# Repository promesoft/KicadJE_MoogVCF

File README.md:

# KicadJE_MoogVCF
Based on https://www.yusynth.net/Modular/Commun/MOOGVCF/Moogfilter-sch.jpg

Based on https://www.yusynth.net/Modular/Commun/WAVEFOLDER/new/JHWavefolder-sch.gif

Based on https://www.yusynth.net/Modular/Commun/ADSR/ADSR555-FINAL.gif

# Status - PCB  in the mail
## Initial 
| Stage  | Detail | Status |
| ------------- | ------------- | ------------- |
| create material  | sch/pcb | OK  |
| | gerber | OK |
| production  |   | Ok |
|  | produced | OK |
|  | delivered | Ok |
## Preliminary validation
| Test  | Detail | Status |
| ------------- | ------------- | ------------- |
| Initial Inspection | | OK - silk messed a bit |
| Initial Technical Test | VCF | CV2 signal issue round Jack |
| Initial Technical Test | ADSR | OK |
| Initial Technical Test | WaveFolder | OK |
| Initial Product Test | VCF | Not working due to missing Caps |
| Initial Product Test | ADSR | OK |
| Initial Product Test | Wavefolder | Works nicely |

## Secondary validation
| Test  | Detail | Status |
| ------------- | ------------- |------------- |
| Product Test | CF | VCF - working ok after botch'ed caps added - no self osc|
| Product Test | ADSR | Works fine after added 100k resistors instead of 0R across 100KB pots |
| Product Test | Wavefolder | nice - no adjustments |
| Quality | VCF | Needs tweaking |
| Quality | ADSR | ADSR interacts when turned all the way down|
| Quality | Wavefolder| Nice |
| Long Term Product Test |  |  |
| Power Draw | VCF | 24mA |
| Power Draw | ADSR | mA |
| Power Draw | Wavefolder | 7mA |

## Errata
### Errata - VCF
 * Missing signal path for CV2 on PCB
 * Missing 2 caps from C207 to R226/227

## Issues and Notes
### VCF
* C214 should be 1206 (its a bit difficult to find 22u 0805 in 16v)
* C211 and C212 should be 1206 or bigger (10u 16v potentially sounds better than 0805)

# Pictures

# Inspiration

# Schematic
## Ladder Filter

## Simple 555 ADSR

## WaveFolder

# Inspiration
 http://jhaible.com/legacy/jh_shaper_B.pdf
 
 https://www.yusynth.net/Modular/Commun/WAVEFOLDER/new/JHWavefolder-sch.gif

 https://www.yusynth.net/Modular/Commun/MOOGVCF/Moogfilter-sch.jpg

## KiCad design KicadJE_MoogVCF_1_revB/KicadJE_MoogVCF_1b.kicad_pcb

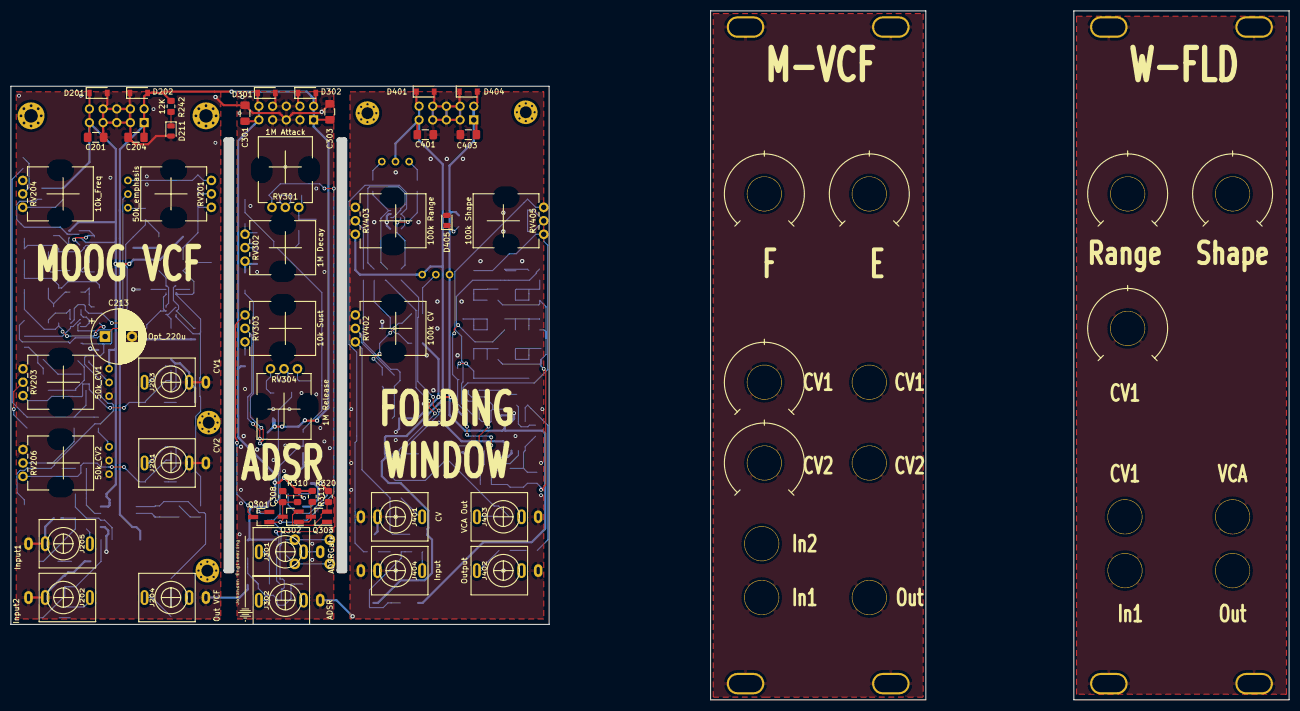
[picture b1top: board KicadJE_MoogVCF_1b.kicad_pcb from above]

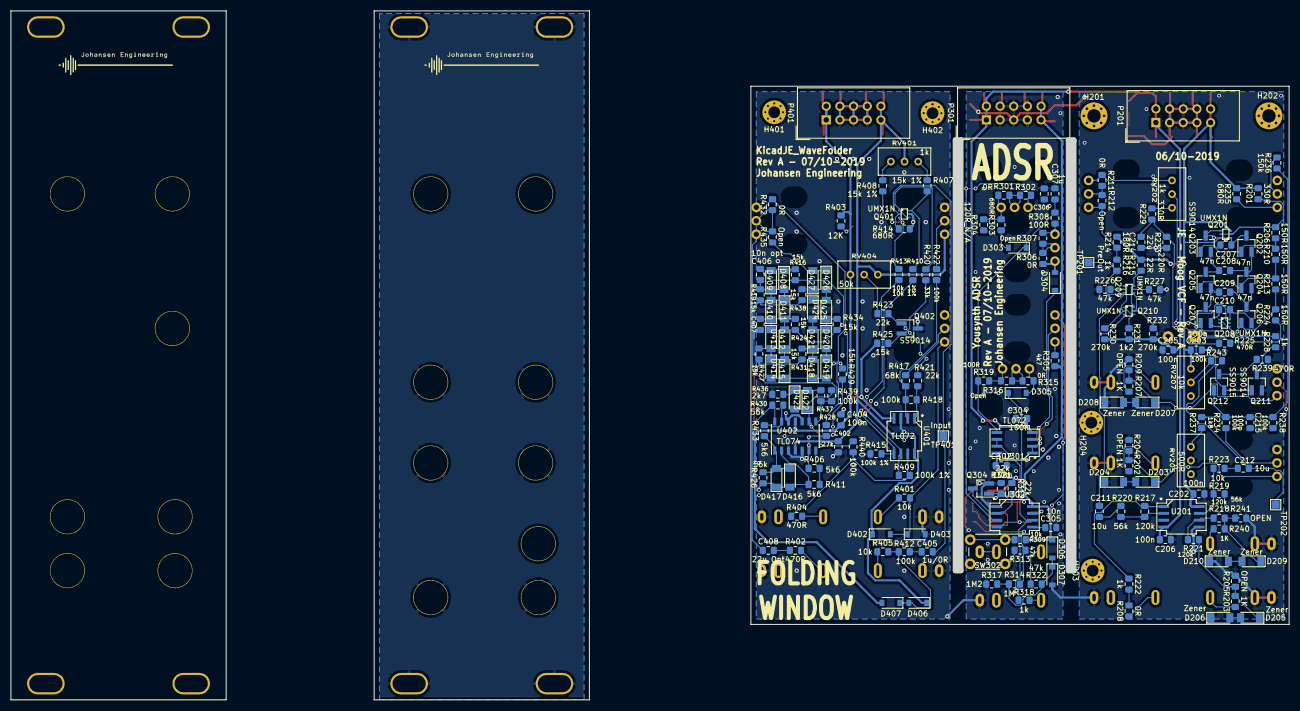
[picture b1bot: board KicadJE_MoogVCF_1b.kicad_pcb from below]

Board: 2 copper layers, 100.0 x 100.0 mm, 245 parts (199 on the bottom side), 135 nets.

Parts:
C201, C204: 10u; C_1206_3216Metric_Pad1.42x1.75mm_HandSolder
C202, C203, C205, C206, C302, C304, C402, C404: 100n; C_0805_2012Metric_Pad1.15x1.40mm_HandSolder
C207, C208, C209, C210: 47n; C_0805_2012Metric_Pad1.15x1.40mm_HandSolder
C211, C212: 10u; C_0805_2012Metric_Pad1.15x1.40mm_HandSolder
C213: Opt_220u; CP_Radial_D10.0mm_P5.00mm
C214: 22u; C_0805_2012Metric_Pad1.15x1.40mm_HandSolder
C215: 100p; C_0805_2012Metric_Pad1.15x1.40mm_HandSolder
C301, C303, C401, C403: 1u; C_1206_3216Metric_Pad1.42x1.75mm_HandSolder
C305, C308: 10n; C_0805_2012Metric_Pad1.15x1.40mm_HandSolder
C306: 10u_N/A; C_0805_2012Metric_Pad1.15x1.40mm_HandSolder
C307: 1u; C_0805_2012Metric_Pad1.15x1.40mm_HandSolder
C405: 1u/0R; C_0805_2012Metric_Pad1.15x1.40mm_HandSolder
C406, C407: 10n opt; C_0805_2012Metric_Pad1.15x1.40mm_HandSolder
C408: 22u Opt; C_0805_2012Metric_Pad1.15x1.40mm_HandSolder
D201, D202, D301, D302, D306, D307, D401, D402, D403, D404, D406, D407: 1N1007; D_SOD-123
D203, D204, D205, D206, D207, D208, D209, D210: Zener; D_MiniMELF
D211, D405: LED; LED_0805_2012Metric
D303, D304, D305: 1N4148; D_SOD-123
D408, D409, D410, D411, D412, D413, D414, D415, D416, D417, D418, D419, D420, D421, D422, D423, D424, D425, D426, D427: LL4148; D_MiniMELF
H201, H202: 2,5mm; MountingHole_2.5mm_Pad_Via
H203, H204, H401, H402: 2,2mm; MountingHole_2.2mm_M2_Pad_Via
J201: CV2; PJ301SM
J202: Input2; PJ301SM
J203: CV1; PJ301SM
J204: Out VCF; PJ301SM
J205: Input1; PJ301SM
J301: ADSRGate; PJ301SM
J302: ADSR; PJ301SM
J401: CV; PJ301SM
J402: Output; PJ301SM
J403: VCA Out; PJ301SM
J404: Input; PJ301SM
P201, P301, P401: Doepfer_Power_10pin; IDC-Header_2x05_Pitch2.54mm_Straight
Q201, Q208, Q209, Q210, Q401: UMX1N; UMX1N_UMT6_DualNPN
Q202, Q203, Q204, Q205, Q206, Q207, Q211, Q402: SS9014; SOT-23_Handsoldering
Q212: SS9015; SOT-23_Handsoldering
Q301: SI2302; SOT-23_Handsoldering
Q302, Q303, Q304: MMBT3904; SOT-23_Handsoldering
R201, R229: 330R; R_0805_2012Metric_Pad1.15x1.40mm_HandSolder
R202, R203, R207, R240: 1K; R_0805_2012Metric_Pad1.15x1.40mm_HandSolder
R204, R205, R209, R241: OPEN; R_0805_2012Metric_Pad1.15x1.40mm_HandSolder
R206, R210, R213, R224: 150R; R_0805_2012Metric_Pad1.15x1.40mm_HandSolder
R208, R211, R301, R306, R315, R432: 0R; R_0805_2012Metric_Pad1.15x1.40mm_HandSolder
R212, R302, R307, R316, R435: Open; R_0805_2012Metric_Pad1.15x1.40mm_HandSolder
R214: 180R; R_0805_2012Metric_Pad1.15x1.40mm_HandSolder
R215: 22R; R_0805_2012Metric_Pad1.15x1.40mm_HandSolder
R216, R222, R228, R318: 1k; R_0805_2012Metric_Pad1.15x1.40mm_HandSolder
R217, R218, R221: 120k; R_0805_2012Metric_Pad1.15x1.40mm_HandSolder
R219, R220, R426, R430: 56k; R_0805_2012Metric_Pad1.15x1.40mm_HandSolder
R223, R309, R401, R405: 10k; R_0805_2012Metric_Pad1.15x1.40mm_HandSolder
R225, R239, R402, R404: 470R; R_0805_2012Metric_Pad1.15x1.40mm_HandSolder
R226, R227, R313, R322: 47k; R_0805_2012Metric_Pad1.15x1.40mm_HandSolder
R230, R232: 270k; R_0805_2012Metric_Pad1.15x1.40mm_HandSolder
R231: 1k2; R_0805_2012Metric_Pad1.15x1.40mm_HandSolder
R233: 220R; R_0805_2012Metric_Pad1.15x1.40mm_HandSolder
R234, R238, R243, R412, R418, R422, R439, R440: 100k; R_0805_2012Metric_Pad1.15x1.40mm_HandSolder
R235, R303, R414: 680R; R_0805_2012Metric_Pad1.15x1.40mm_HandSolder
R236: 150k; R_0805_2012Metric_Pad1.15x1.40mm_HandSolder
R237: 1k8; R_0805_2012Metric_Pad1.15x1.40mm_HandSolder
R242, R403: 12K; R_0805_2012Metric_Pad1.15x1.40mm_HandSolder
R304: 120R_N/A; R_0805_2012Metric_Pad1.15x1.40mm_HandSolder
R305: 4k7; R_0805_2012Metric_Pad1.15x1.40mm_HandSolder
R308, R319: 100R; R_0805_2012Metric_Pad1.15x1.40mm_HandSolder
R310, R311, R312, R321, R421, R423: 22k; R_0805_2012Metric_Pad1.15x1.40mm_HandSolder
R314: 1M; R_0805_2012Metric_Pad1.15x1.40mm_HandSolder
R317: 1M2; R_0805_2012Metric_Pad1.15x1.40mm_HandSolder
R320: 10R; R_0805_2012Metric_Pad1.15x1.40mm_HandSolder
R406, R411, R433: 5k6; R_0805_2012Metric_Pad1.15x1.40mm_HandSolder
R407, R408: 15k 1%; R_0805_2012Metric_Pad1.15x1.40mm_HandSolder
R409, R415: 100k 1%; R_0805_2012Metric_Pad1.15x1.40mm_HandSolder
R410, R413: 10k 1%; R_0805_2012Metric_Pad1.15x1.40mm_HandSolder
R416, R419, R424, R425, R427, R429, R431, R434, R438: 15k; R_0805_2012Metric_Pad1.15x1.40mm_HandSolder
R417: 68k; R_0805_2012Metric_Pad1.15x1.40mm_HandSolder
R420, R437: 33k; R_0805_2012Metric_Pad1.15x1.40mm_HandSolder
R428: 27k; R_0805_2012Metric_Pad1.15x1.40mm_HandSolder
R436: 2k7; R_0805_2012Metric_Pad1.15x1.40mm_HandSolder
RV201: 50k_emphasis; Potentiometer_China_RK09_Single_Vertical_AJ
RV202, RV401: 1k; Bourns3296WV
RV203: 50k_CV1; Potentiometer_China_RK09_Single_Vertical_AJ
RV204: 10k_Freq; Potentiometer_China_RK09_Single_Vertical_AJ
RV205: 500R; Bourns3296WV
RV206: 50k_CV2; Potentiometer_China_RK09_Single_Vertical_AJ
RV207: 10k; Bourns3296WV
RV301: 1M Attack; Potentiometer_China_RK09_Single_Vertical_AJ
RV302: 1M Decay; Potentiometer_China_RK09_Single_Vertical_AJ
RV303: 10k Sust; Potentiometer_China_RK09_Single_Vertical_AJ
RV304: 1M Release; Potentiometer_China_RK09_Single_Vertical_AJ
RV402: 100k CV; Potentiometer_China_RK09_Single_Vertical_AJ
RV403: 100k Range; Potentiometer_China_RK09_Single_Vertical_AJ
RV404: 50k; Bourns3296WV
RV405: 100k Shape; Potentiometer_China_RK09_Single_Vertical_AJ
SW301: SW_DPDT_x2; Johansen_engineering_logo_20mm
SW302: Gate; SW_PUSH_6mm
TP201: PreOut; TestPoint_Pad_1.5x1.5mm
TP202, TP401: Input; TestPoint_Pad_1.5x1.5mm
U201, U301, U401: TL072; AJ_SO-8_5.3x6.2mm_P1.27mm
U302: TLC555; AJ_SO-8_5.3x6.2mm_P1.27mm
U402: TL074; SOIC-14_3.9x8.7mm_P1.27mm

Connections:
555_Dis: Q301.2, U302.7
555_Out: R302.1, RV301.3, U302.3
555_RST: C308.2, D305.1, Q301.1, Q302.3, R310.2, U302.4
555_Threshold: R318.2, U301.6, U301.7, U302.6
555_Trig: Q304.3, R312.2, U302.2
+12V: C201.2, C202.2, C203.2, C301.2, C302.2, C401.2, C402.2, D201.1, D301.1, D306.1, D401.1, D402.1, D406.1, P201.9, P201.10, P301.9, P301.10, P401.9, P401.10, Q201.3, Q201.6, R201.2, R214.2, R215.2, R235.2, R305.1, R309.1, R310.1, R311.1, R312.1, RV207.1, RV401.2, RV403.1, RV404.3, U201.8, U301.8, U302.8, U401.8, U402.4
-12V: C204.1, C205.1, C206.1, C303.2, C304.2, C403.2, C404.2, D202.2, D302.2, D404.2, D407.2, P201.1, P201.2, P301.1, P301.2, P401.1, P401.2, R230.1, R231.1, R232.1, R242.1, R403.1, R425.1, RV404.1, U201.4, U301.4, U401.4, U402.11
/KicadJE_Yousynth_MoogVCF/Coupling: R212.1, R214.1, R216.1, RV201.3
/KicadJE_Yousynth_MoogVCF/PNP_B: C215.2, Q212.1, R234.2, R236.1, R237.2, R238.2
/KicadJE_Yousynth_MoogVCF/PNP_E: Q211.1, Q212.2, R243.1
ADSRGate: D306.2, D307.1, R314.2, R317.2, R322.2
ADSR_out: J302.T, R318.1
CV1: D207.1, R207.2, R209.1, RV203.1
CV2: D203.1, R202.2, R204.1, RV206.1
CV_Fold: D402.2, D403.1, R401.2, RV402.1
GND: C201.1, C202.1, C203.1, C204.2, C205.2, C206.2, C213.2, C214.1, C215.1, C301.1, C302.1, C303.1, C304.1, C305.2, C306.1, C307.1, C401.1, C402.1, C403.1, C404.1, D201.2, D202.1, D204.1, D206.1, D208.1, D210.1, D211.2, D301.2, D302.1, D307.2, D401.2, D403.2, D404.1, D405.2, J201.S, J201.TN, J202.S, J202.TN, J203.S, J203.TN, J204.S, J205.S, J205.TN, J302.S, J401.S, J401.TN, J402.S, J403.S, J404.S, J404.TN, P201.3, P201.4, P201.5, P201.6, P201.7, P201.8, P301.3, P301.4, P301.5, P301.6, P301.7, P301.8, P401.3, P401.4, P401.5, P401.6, P401.7, P401.8, Q211.2, Q304.2, Q401.5, Q402.3, R204.2, R205.2, R209.2, R226.1, R227.1, R233.1, R239.1, R241.2, R317.1, R320.2, R321.2, R414.1, R415.1, R436.1, RV203.3, RV204.3, RV205.2, RV205.3, RV206.3, RV207.3, RV402.3, RV403.3, U201.3, U201.5, U302.1, U401.3, U402.3, U402.5, U402.10, U402.12
InAudio1: D209.1, R218.1, R240.2, R241.1
InAudio2: D205.1, R203.2, R205.1, R221.1
Input_Fold: D406.2, D407.1, R405.2, R412.2
unnamed: C207.1, Q201.4, Q203.3
unnamed: C207.2, Q201.1, Q202.3
unnamed: C208.1, Q203.2, Q205.3
unnamed: C208.2, Q202.2, Q204.3
unnamed: C209.1, Q205.2, Q207.3
unnamed: C209.2, Q204.2, Q206.3
unnamed: C210.1, Q207.2, Q208.3
unnamed: C210.2, Q206.2, Q208.6
unnamed: C211.1, R220.1
unnamed: C211.2, Q209.3, Q210.3, R216.2, TP201.1
unnamed: C212.1, Q208.2, R225.2, TP202.1
unnamed: C212.2, R223.2
unnamed: C213.1, C214.2, R224.1, R225.1, R229.1, R233.2
unnamed: C305.1, U302.5
unnamed: C307.2, D303.1, R308.1, R319.1, U301.5
unnamed: C308.1, Q304.1, R321.1
unnamed: C405.1, Q401.2, R414.2, TP401.1
unnamed: C405.2, R412.1
unnamed: C406.1, D408.2, D409.1, D410.2, D411.1, R419.1
unnamed: C406.2, R406.1, R416.2, R424.2, R428.2, R429.2, R434.2, U402.6
unnamed: C407.1, D416.2, D417.1, R411.2, R419.2, R426.1, R427.2, R431.2, R438.2, U402.2
unnamed: C407.2, D410.1, D411.2, D412.1, D413.2, R424.1
unnamed: C408.1, R430.2, U402.14
unnamed: D203.2, D204.2
unnamed: D205.2, D206.2
unnamed: D207.2, D208.2
unnamed: D209.2, D210.2
unnamed: D211.1, R242.2
unnamed: D303.2, R303.2
unnamed: D304.1, U301.1, U301.2
unnamed: D304.2, R306.1, RV302.1
unnamed: D305.2, R315.1, RV304.1
unnamed: D405.1, R403.2
unnamed: D408.1, D409.2, R416.1
unnamed: D412.2, D413.1, D414.2, D415.1, R427.1
unnamed: D414.1, D415.2, D418.1, D419.2, R429.1
unnamed: D416.1, D417.2, R426.2, R433.1, U402.1
unnamed: D418.2, D419.1, D420.2, D421.1, R431.1
unnamed: D420.1, D421.2, D424.1, D425.2, R434.1
unnamed: D422.1, D423.2, R436.2, R437.2
unnamed: D422.2, D423.1, R439.2, R440.1, U402.9
unnamed: D424.2, D425.1, D426.2, D427.1, R438.1
unnamed: D426.1, D427.2, R435.1, R437.1, R439.1, RV405.3, U402.8
unnamed: J201.T, R202.1
unnamed: J202.T, R203.1
unnamed: J203.T, R207.1
unnamed: J204.T, R208.1
unnamed: J205.T, R240.1
unnamed: J301.S, J301.TN
unnamed: J301.T, R322.1
unnamed: J401.T, R401.1
unnamed: J402.T, R402.2
unnamed: J403.T, R404.2
unnamed: J404.T, R405.1
unnamed: Q201.2, Q201.5, R201.1, R206.2
unnamed: Q202.1, Q203.1, R206.1, R210.2
unnamed: Q204.1, Q205.1, R210.1, R213.2
unnamed: Q206.1, Q207.1, R213.1, R224.2
unnamed: Q208.1, Q208.4, R228.2
unnamed: Q208.5, RV202.2
unnamed: Q209.1, Q210.2, R230.2
unnamed: Q209.2, R226.2
unnamed: Q209.4, Q210.5, R232.2
unnamed: Q209.5, R227.2
unnamed: Q209.6, Q210.6, R215.1
unnamed: Q210.1, Q210.4, R231.2
unnamed: Q211.3, R228.1
unnamed: Q212.3, R239.2
unnamed: Q301.3, RV303.3
unnamed: Q302.1, Q303.3, R311.2
unnamed: Q302.2, Q303.2, R320.1
unnamed: Q303.1, R313.1, R314.1
unnamed: Q401.1, Q401.4, R420.2
unnamed: Q401.3, R408.1, R413.2
unnamed: Q401.6, R407.1, R410.2
unnamed: Q402.1, R421.1, R423.2
unnamed: Q402.2, R420.1, R425.2
unnamed: R211.1, RV201.1, RV202.1
unnamed: R211.2, R212.2, RV201.2
unnamed: R217.1, R220.2, U201.2
unnamed: R217.2, R222.1, U201.1
unnamed: R218.2, R219.1, R221.2, U201.6
unnamed: R219.2, R223.1, U201.7
unnamed: R229.2, RV202.3
unnamed: R234.1, RV206.2
unnamed: R235.1, RV204.1
unnamed: R236.2, RV204.2
unnamed: R237.1, RV205.1
unnamed: R238.1, RV203.2
unnamed: R243.2, RV207.2
unnamed: R301.1, R303.1, R304.1, RV301.1
unnamed: R301.2, R302.2, RV301.2
unnamed: R305.2, RV303.1
unnamed: R306.2, R307.2, RV302.2
unnamed: R307.1, R308.2, RV302.3
unnamed: R309.2, SW302.2
unnamed: R313.2, SW302.1
unnamed: R315.2, R316.2, RV304.2
unnamed: R316.1, R319.2, RV304.3
unnamed: R406.2, R411.1, U402.7
unnamed: R407.2, RV401.3
unnamed: R408.2, RV401.1
unnamed: R409.2, R410.1, U401.6
unnamed: R413.1, R415.2, U401.5
unnamed: R417.1, R418.2, R422.2, U401.2
unnamed: R417.2, RV402.2
unnamed: R418.1, R421.2, U401.1
unnamed: R422.1, RV403.2
unnamed: R423.1, RV404.2
unnamed: R428.1, R432.2, RV405.1
unnamed: R430.1, R433.2, U402.13
unnamed: R432.1, R435.2, RV405.2
unnamed: RV303.2, U301.3
OutVCF: R208.2, R222.2
Output_Fold: C408.2, R402.1
Output_VCA: R404.1, R409.1, R440.2, U401.7

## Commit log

2019-10-06 Startup
2019-10-06 acq from Ate0Ate
2019-10-06 diff stage sch
2019-10-06 Moog Output stage
2019-10-06 Footprints
2019-10-06 Placing components
2019-10-06 fixing links
2019-10-06 placing input prot
2019-10-06 all components placed
2019-10-06 Moog VCF complete
2019-10-06 Labels complete on Moog
2019-10-06 forgot a trimmer
2019-10-06 Trim added to PCB
2019-10-06 Yousynth ADSR initiated
2019-10-06 ADSR sch done
2019-10-07 ADSR Routed
2019-10-07 Labels ADSR
2019-10-07 Inspiration
2019-10-07 Wavefolder sch taking form
2019-10-07 Wavefolder annotated
2019-10-07 ERC done
2019-10-07 Fix power bug in ADSR TL072
2019-10-07 Folding Diode conn missing
2019-10-07 Routed Wavefolder
2019-10-07 Wavefolder labeled
2019-10-07 Gerber
2019-10-07 zip for jlc
2019-10-07 remove excess btn
2020-02-05 Review R-Open names after initial assembley - ADSR
2020-02-12 RevB
    Missing 2x 220N from filter to output :-S
2020-02-15 revb update
2020-04-10 Pictures
2020-04-10 RevB init
2021-05-17 Faceplate for Moog Filter
2021-05-17 Wavefolder Faceplate
2021-05-17 Update README.md
    KicadJE_MoogVCF_1_revB/KicadJE_MoogVCF_1b_Wavefolder_Front.png
2021-05-17 Update fp-info-cache
